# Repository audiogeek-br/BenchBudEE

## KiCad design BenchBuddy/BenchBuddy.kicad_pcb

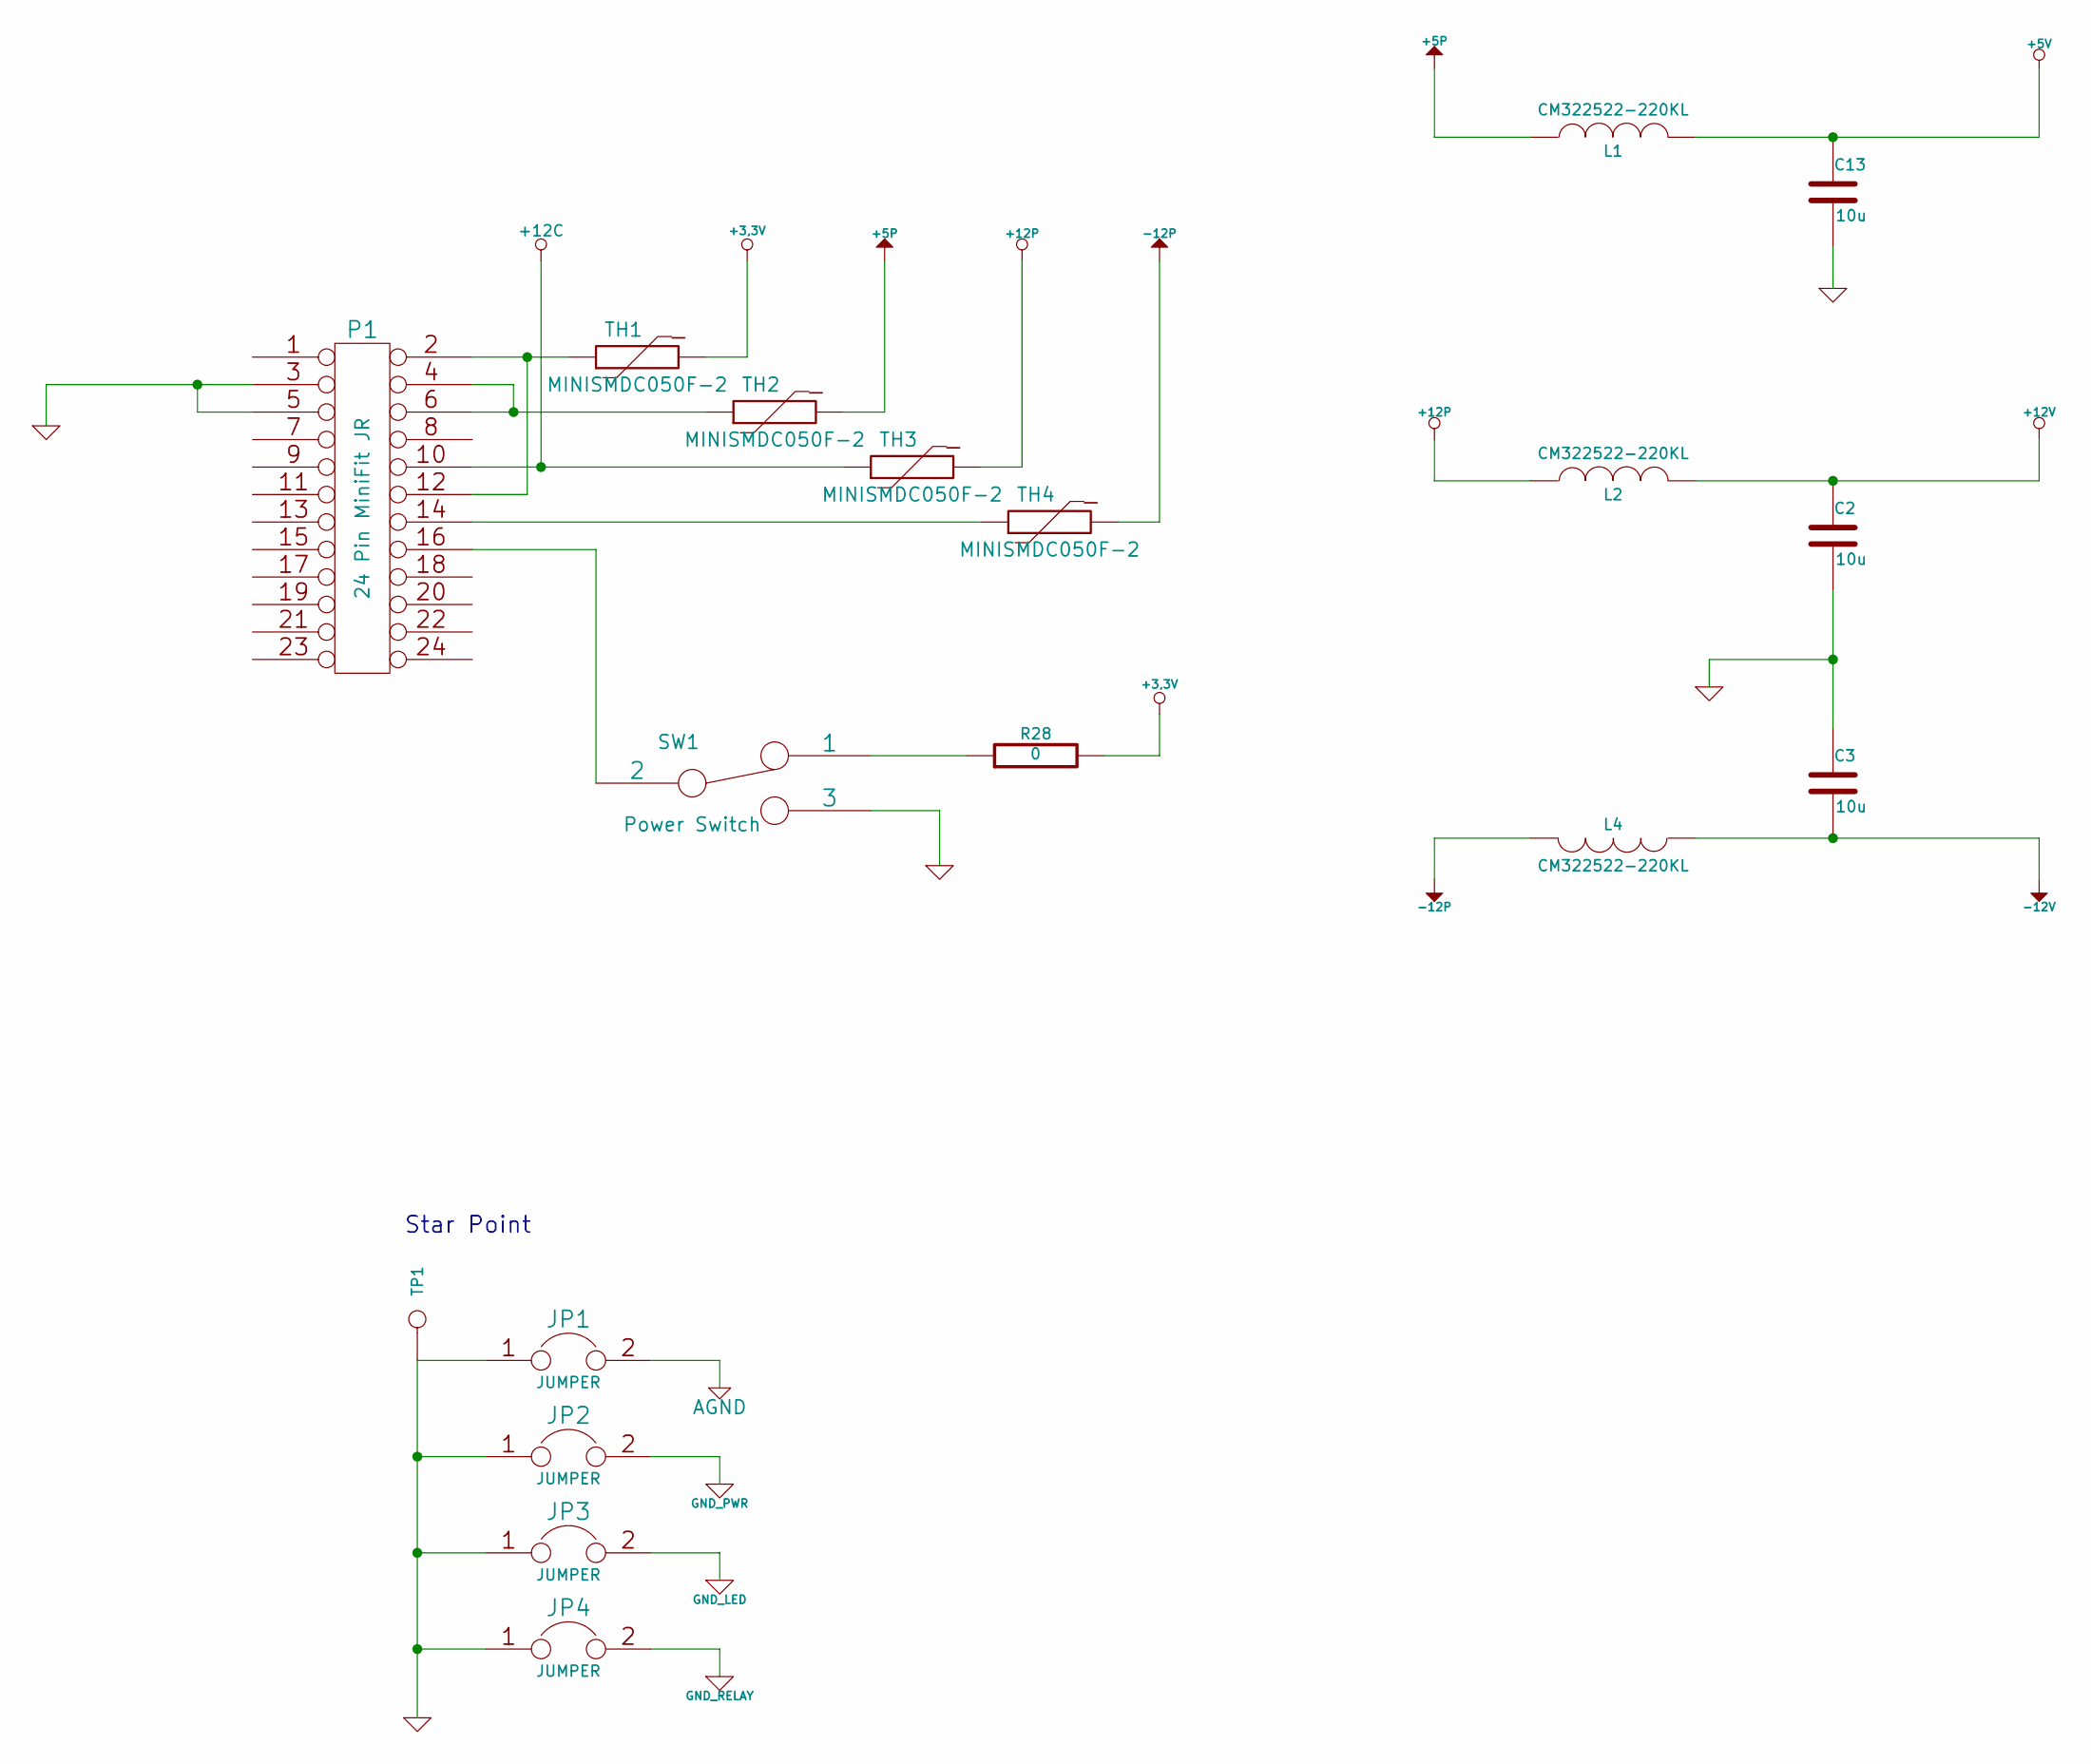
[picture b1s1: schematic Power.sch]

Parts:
C2, C3, C13: 10u
JP1, JP2, JP3, JP4: JUMPER
L1, L2, L4: CM322522-220KL; MFG Part Number CM322522-220KL
P1: 24 Pin MiniFit JR; MFG Part Number 0039301240
R28: 0
SW1: Power Switch; MFG Part Number OS102011MA1QN1
TH1, TH2, TH3, TH4: MINISMDC050F-2; MFG Part Number MINISMDC050F-2
TP1: CONN_1

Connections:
+3.3V: R28.2, TH1.2; also elsewhere on the board
+5P: L1.1, TH2.2; also elsewhere on the board
+5V: C13.1, L1.2; also elsewhere on the board
+12C: P1.10, TH3.1; also elsewhere on the board
+12P: L2.1, TH3.2; also elsewhere on the board
+12V: C2.1, L2.2; also elsewhere on the board
-12P: L4.2, TH4.2
-12V: C3.2, L4.1; also elsewhere on the board
AGND: JP1.2; also elsewhere on the board
GND: C2.2, C3.1, C13.2, JP1.1, JP2.1, JP3.1, JP4.1, P1.3, P1.5, SW1.3, TP1.1; also elsewhere on the board
unnamed: P1.16, SW1.2
unnamed: R28.1, SW1.1
unnamed: P1.14, TH4.1
unnamed: P1.4, P1.6, TH2.1
unnamed: P1.2, P1.12, TH1.1

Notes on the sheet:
Star Point

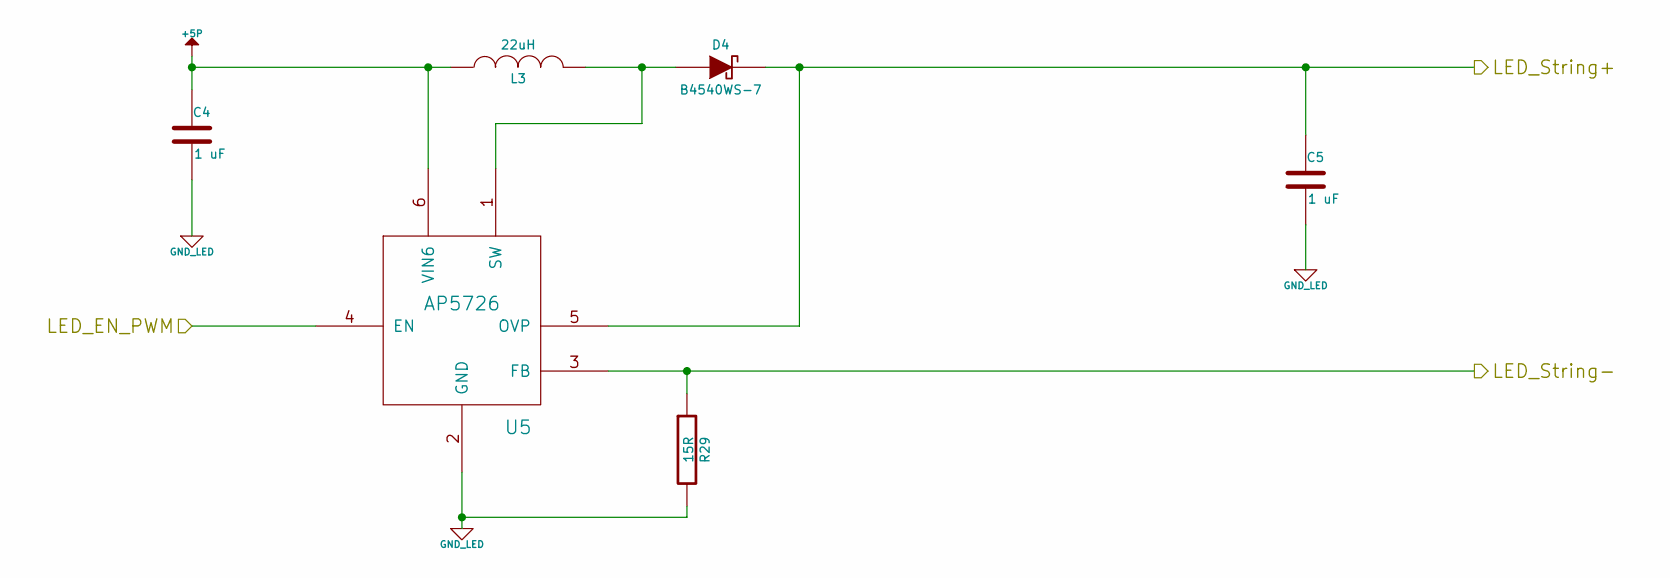
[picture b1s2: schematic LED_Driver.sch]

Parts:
C4, C5: 1 uF
D4: B4540WS-7
L3: 22uH; MFG Part Number NR4012T220M
R29: 15R
U5: AP5726

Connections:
+5P: C4.1, L3.1, U5.6 (VIN6); also elsewhere on the board
/Arduino/LED_EN_PWM: U5.4 (EN); also elsewhere on the board
/Terminal Block/LED_STRING+: C5.1, D4.2 (K), U5.5 (OVP); also elsewhere on the board
/Terminal Block/LED_STRING-: R29.1, U5.3 (FB); also elsewhere on the board
GND_LED: C4.2, C5.2, R29.2, U5.2 (GND)
unnamed: D4.1 (A), L3.2, U5.1 (SW)

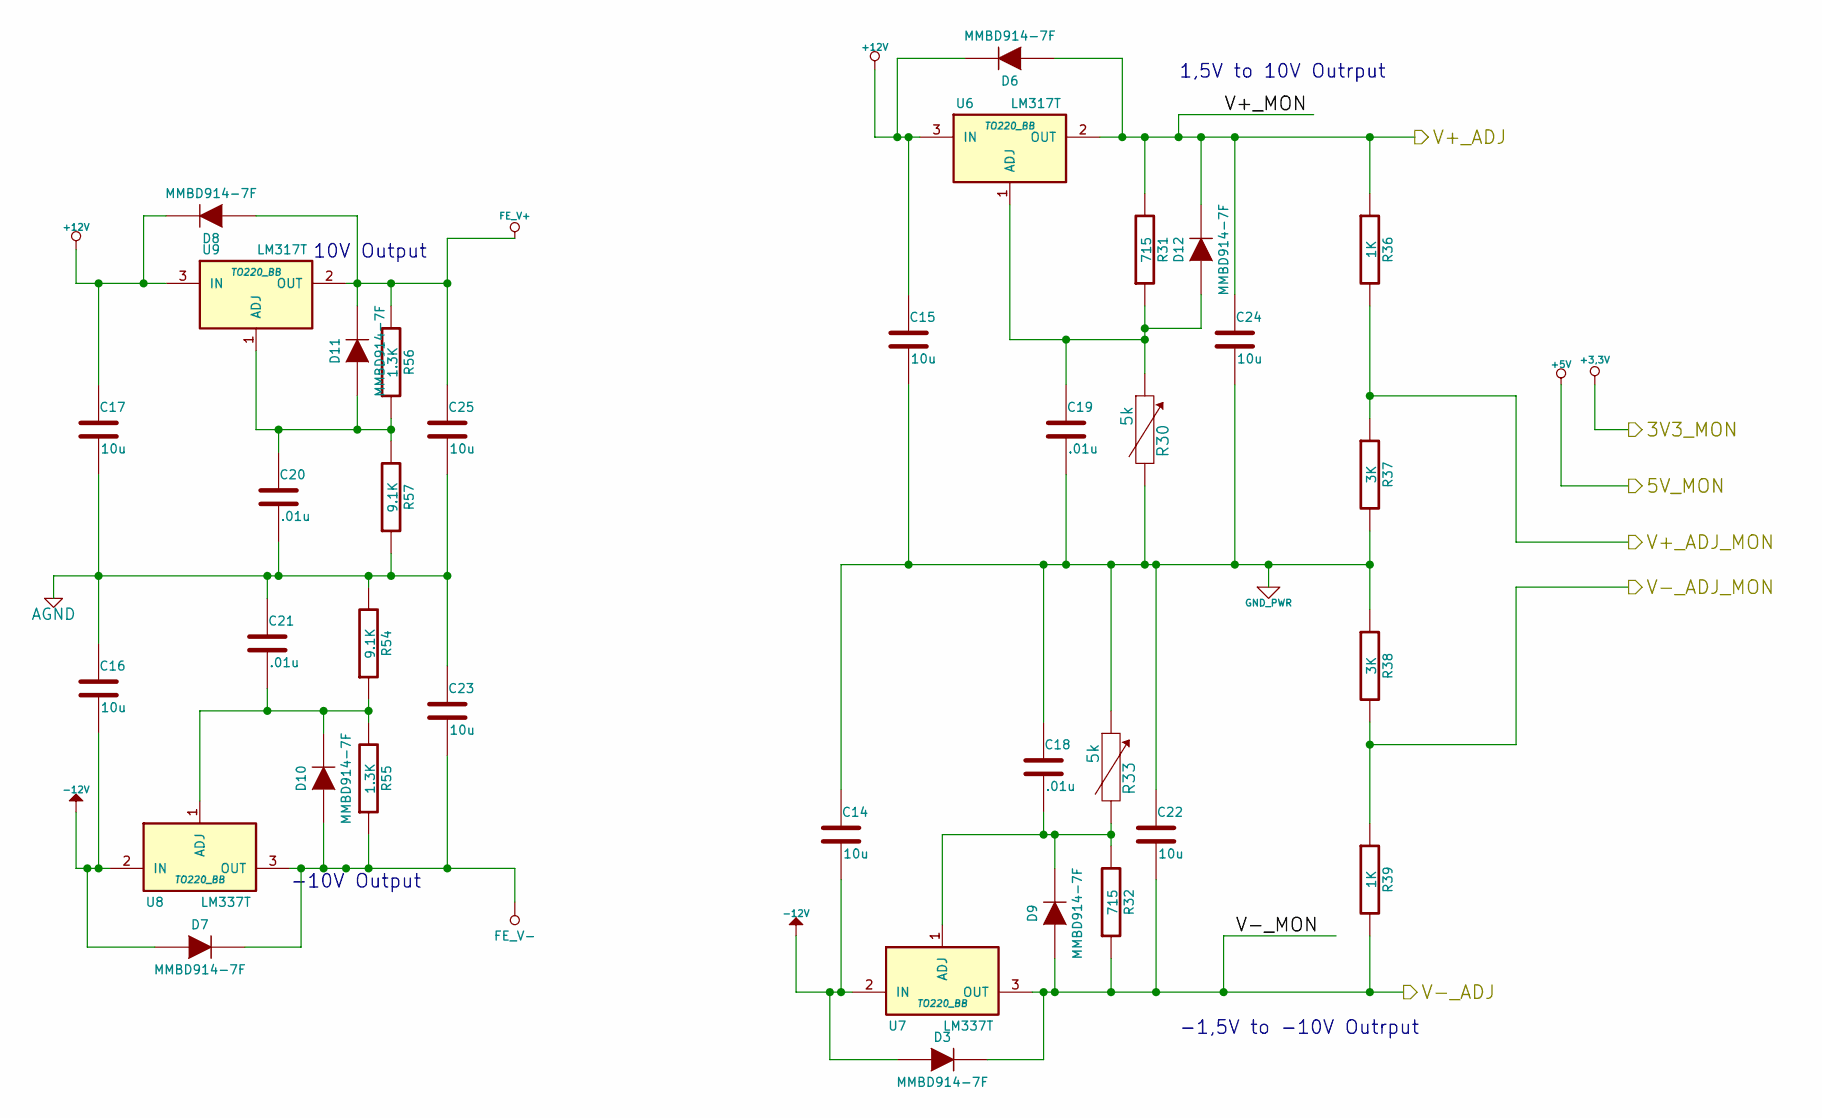
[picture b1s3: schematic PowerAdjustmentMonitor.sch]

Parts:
C14, C15, C16, C17, C22, C23, C24, C25: 10u
C18, C19, C20, C21: .01u
D3, D6, D7, D8, D9, D10, D11, D12: MMBD914-7F
R30, R33: 5k
R31, R32: 715
R36, R39: 1K
R37, R38: 3K
R54, R57: 9.1K
R55, R56: 1.3K
U6, U9: LM317T; TO220_BB
U7, U8: LM337T; TO220_BB

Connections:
+12V: C15.1, C17.1, D6.2 (K), D8.2 (K), U6.3 (IN), U9.3 (IN); also elsewhere on the board
-12V: C14.2, C16.2, D3.1 (A), D7.1 (A), U7.2 (IN), U8.2 (IN); also elsewhere on the board
/Arduino/V+_ADJ_MON: R36.2, R37.1; also elsewhere on the board
/Arduino/V-_ADJ_MON: R38.2, R39.1; also elsewhere on the board
/PowerAdjustmentMonitor/V+_ADJ: C24.1, D6.1 (A), D12.2 (K), R31.2, R36.1, U6.2 (OUT); also elsewhere on the board
/PowerAdjustmentMonitor/V-_ADJ: C22.2, D3.2 (K), D9.1 (A), R32.1, R39.2, U7.3 (OUT); also elsewhere on the board
AGND: C16.1, C17.2, C20.2, C21.1, C23.1, C25.2, R54.2, R57.1; also elsewhere on the board
FE_V+: C25.1, D8.1 (A), D11.2 (K), R56.2, U9.2 (OUT); also elsewhere on the board
FE_V-: C23.2, D7.2 (K), D10.1 (A), R55.1, U8.3 (OUT); also elsewhere on the board
GND_PWR: C14.1, C15.2, C18.1, C19.2, C22.1, C24.2, R30.2, R33.1, R37.2, R38.1; also elsewhere on the board
unnamed: C21.2, D10.2 (K), R54.1, R55.2, U8.1 (ADJ)
unnamed: C20.1, D11.1 (A), R56.1, R57.2, U9.1 (ADJ)
unnamed: C19.1, D12.1 (A), R30.1, R31.1, U6.1 (ADJ)
unnamed: C18.2, D9.2 (K), R32.2, R33.2, U7.1 (ADJ)

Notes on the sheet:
10V Output
1,5V to 10V Outrput
-10V Output
-1,5V to -10V Outrput

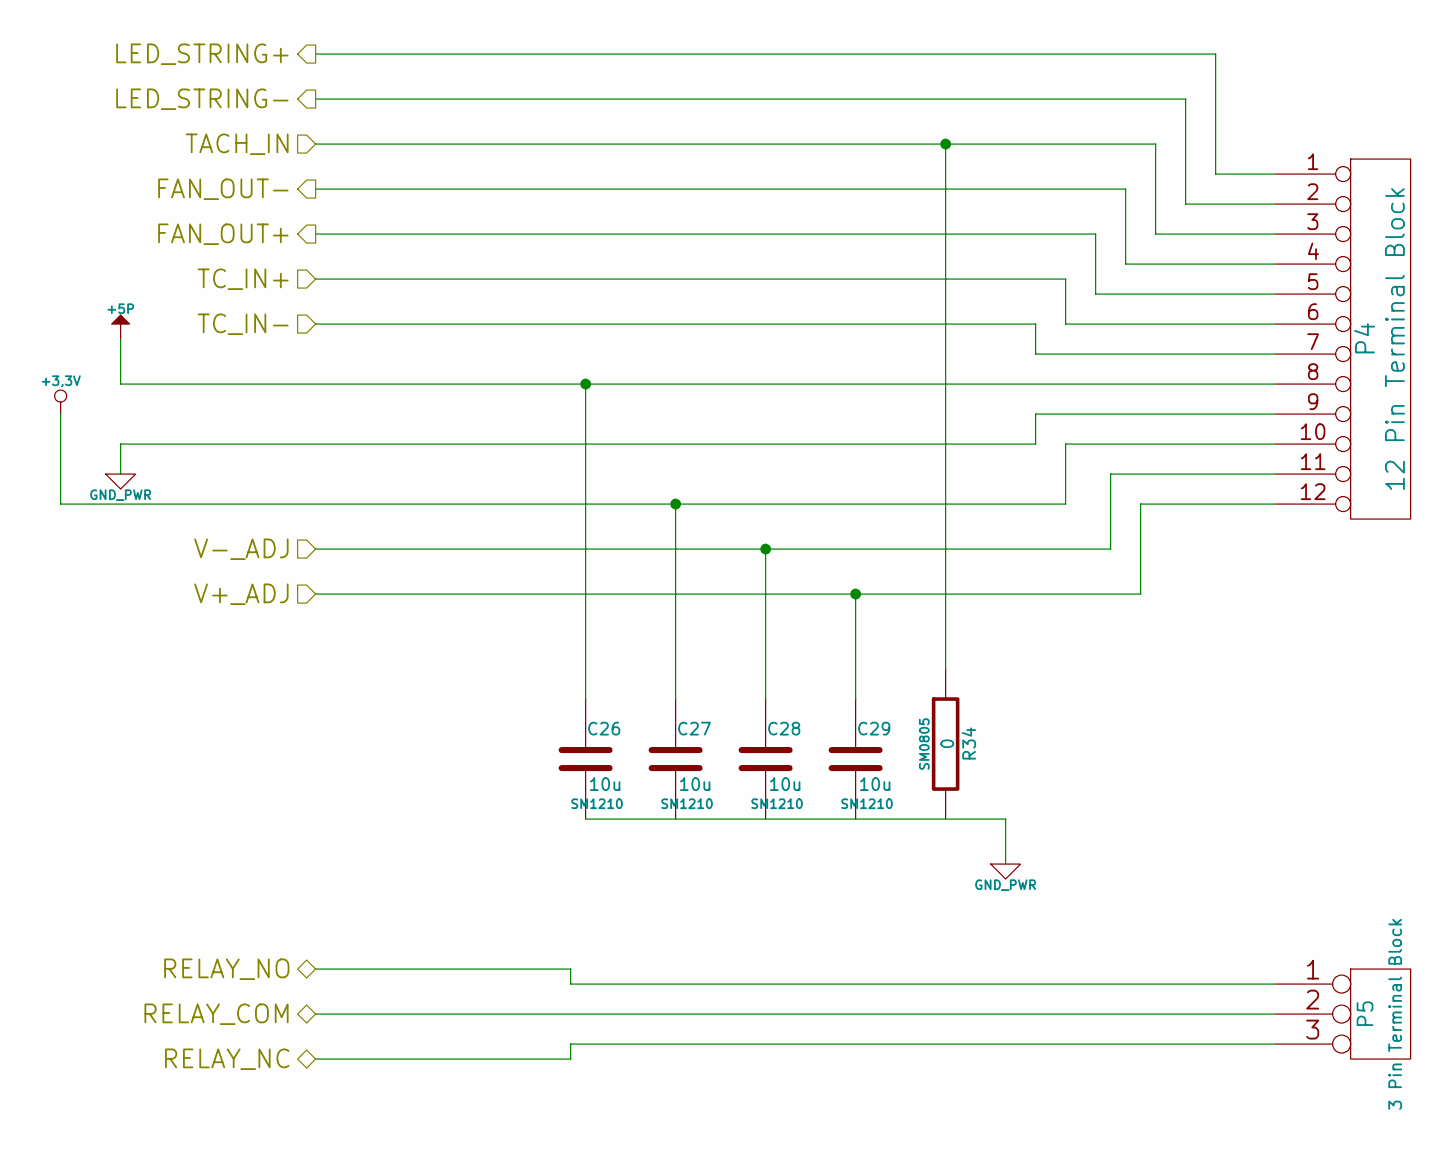
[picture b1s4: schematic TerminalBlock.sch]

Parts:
C26, C27, C28, C29: 10u; SM1210
P4: 12 Pin Terminal Block; MFG Part Number OSTTE120104
P5: 3 Pin Terminal Block; MFG Part Number 1935174
R34: 0; SM0805

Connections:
+3.3V: C27.1, P4.10; also elsewhere on the board
+5P: C26.1, P4.8; also elsewhere on the board
/PowerAdjustmentMonitor/V+_ADJ: C29.1, P4.12; also elsewhere on the board
/PowerAdjustmentMonitor/V-_ADJ: C28.1, P4.11; also elsewhere on the board
/Relay/RELAY_COM: P5.2 (PM); also elsewhere on the board
/Relay/RELAY_NC: P5.3; also elsewhere on the board
/Relay/RELAY_NO: P5.1; also elsewhere on the board
/Terminal Block/FAN_OUT+: P4.5; also elsewhere on the board
/Terminal Block/FAN_OUT-: P4.4; also elsewhere on the board
/Terminal Block/LED_STRING+: P4.1; also elsewhere on the board
/Terminal Block/LED_STRING-: P4.2; also elsewhere on the board
/Terminal Block/TACH_IN: P4.3, R34.1; also elsewhere on the board
/Thermocoulpe/TC IN +: P4.6; also elsewhere on the board
/Thermocoulpe/TC IN -: P4.7; also elsewhere on the board
GND_PWR: C26.2, P4.9; also elsewhere on the board

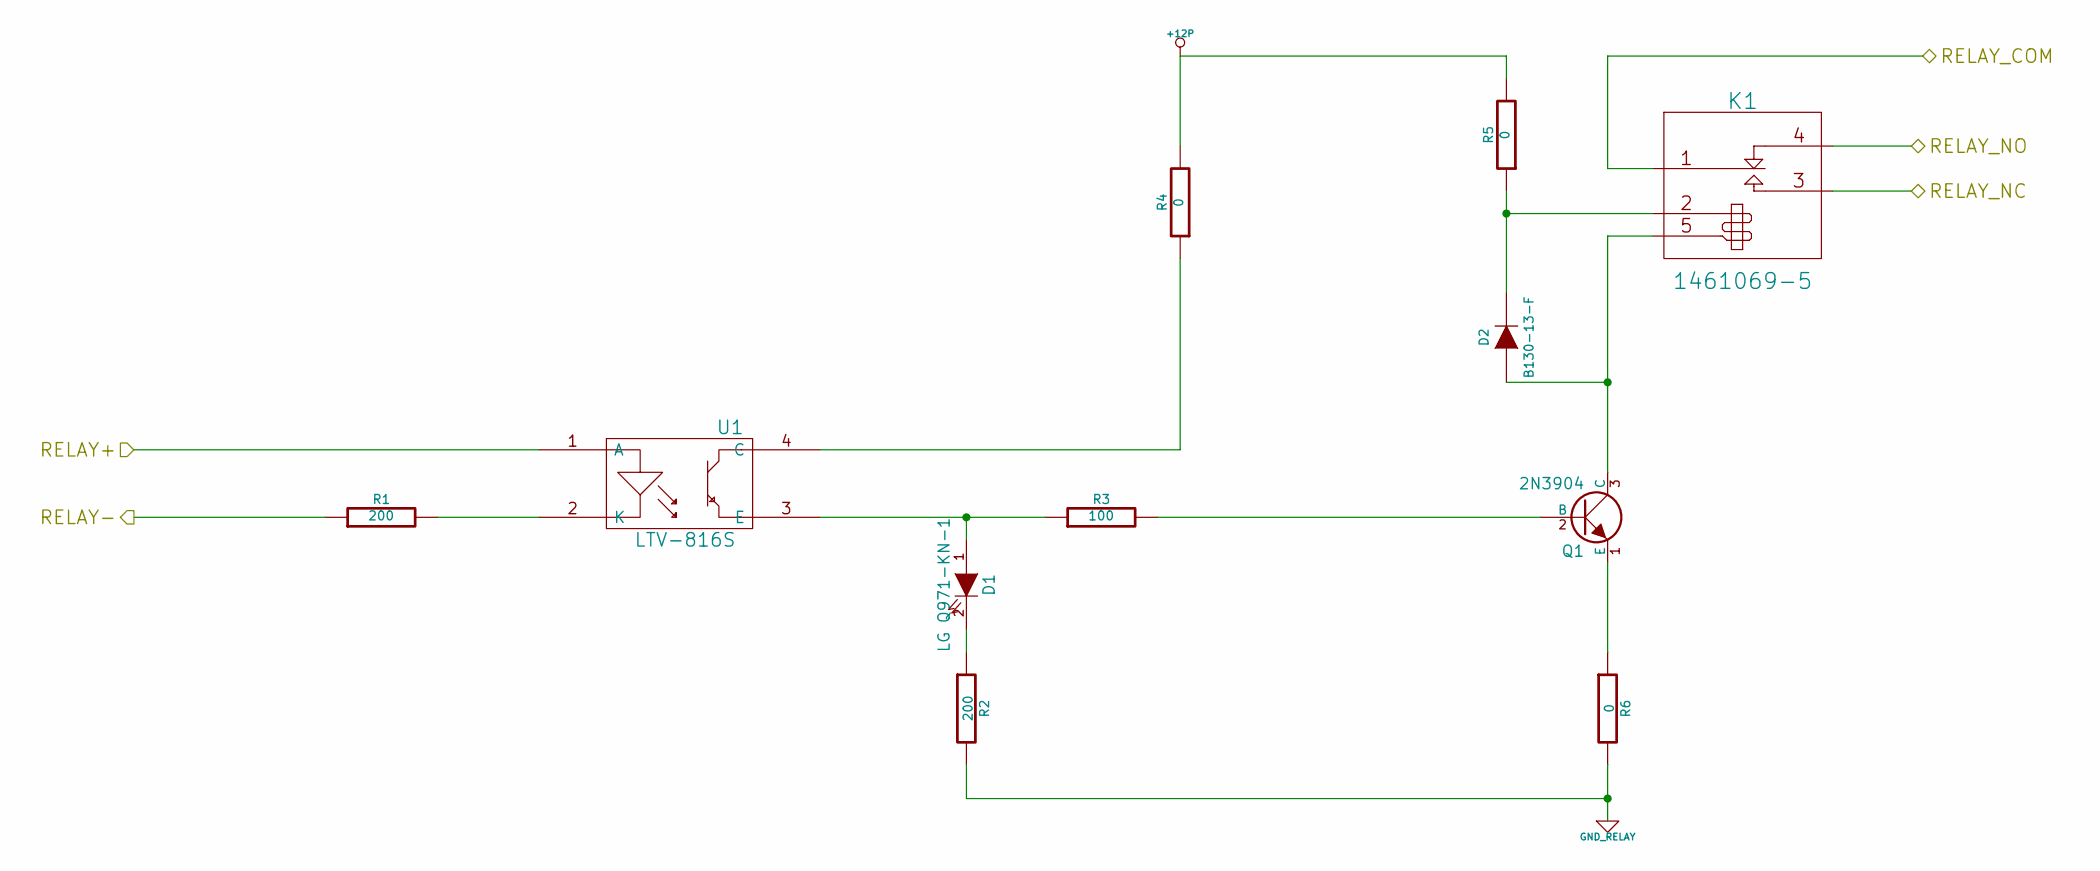
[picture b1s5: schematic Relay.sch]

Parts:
D1: LG Q971-KN-1
D2: B130-13-F
K1: 1461069-5
Q1: 2N3904; MFG Part Number MMBT3904-7-F
R1, R2: 200
R3: 100
R4, R5, R6: 0
U1: LTV-816S; MFG Part Number LTV-816S

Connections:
+12P: R4.2, R5.2; also elsewhere on the board
/Arduino/RELAY+: U1.1 (A); also elsewhere on the board
/Arduino/RELAY-: R1.1; also elsewhere on the board
/Relay/RELAY_COM: K1.1 (COM); also elsewhere on the board
/Relay/RELAY_NC: K1.3 (NO); also elsewhere on the board
/Relay/RELAY_NO: K1.4 (NC); also elsewhere on the board
GND_RELAY: R2.2, R6.2
unnamed: D1.2 (K), R2.1
unnamed: D2.2 (K), K1.2 (COIL_+), R5.1
unnamed: Q1.2 (B), R3.2
unnamed: Q1.1 (E), R6.1
unnamed: D1.1 (A), R3.1, U1.3 (E)
unnamed: R1.2, U1.2 (K)
unnamed: R4.1, U1.4 (C)
unnamed: D2.1 (A), K1.5 (COIL_-), Q1.3 (C)

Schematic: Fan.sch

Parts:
C11, C12, C32: 1u
D5: B130-13-F; MFG Part Number B130-13-F
Q2: DMN65D8L-7; MFG Part Number DMN65D8L-7
Q3, Q4: AOD476; MFG Part Number AOD476
R35, R40, R58, R59: 0
R41: 1
TH5: MINISMDC050F-2; MFG Part Number MINISMDC050F-2
U4: OPA4170
U11: MCP4801

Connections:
+5V: C11.1, U11.1 (Vdd); also elsewhere on the board
+12C: C12.1, TH5.1; also elsewhere on the board
/Arduino/CURR_MEAS: Q3.2, Q4.3, R41.1, R59.2; also elsewhere on the board
/Arduino/FAN_MODE: Q3.1; also elsewhere on the board
/Arduino/FAN_PWM: Q2.G; also elsewhere on the board
/Arduino/MOSI: U11.4 (SDI); also elsewhere on the board
/Arduino/SCLK: U11.3 (SCK); also elsewhere on the board
/Arduino/~LADC: U11.5 (~LDAC); also elsewhere on the board
/Arduino/~SHDN: U11.6 (~SHDN); also elsewhere on the board
/Fan/CS_N: U11.2 (~CS); also elsewhere on the board
/Terminal Block/FAN_OUT+: D5.2 (K), TH5.2; also elsewhere on the board
/Terminal Block/FAN_OUT-: D5.1 (A), Q4.2; also elsewhere on the board
AGND: C12.2, Q3.3, R35.2, R41.2, U11.7 (Vss); also elsewhere on the board
FE_V+: U4.4 (V+); also elsewhere on the board
FE_V-: U4.11 (V-); also elsewhere on the board
unnamed: Q2.S, R35.1
unnamed: C32.1, R58.1, U4.7
unnamed: C32.2, R59.1, U4.6 (-)
unnamed: R40.1, U11.8 (Vout)
unnamed: Q2.D, R40.2, U4.5 (+)

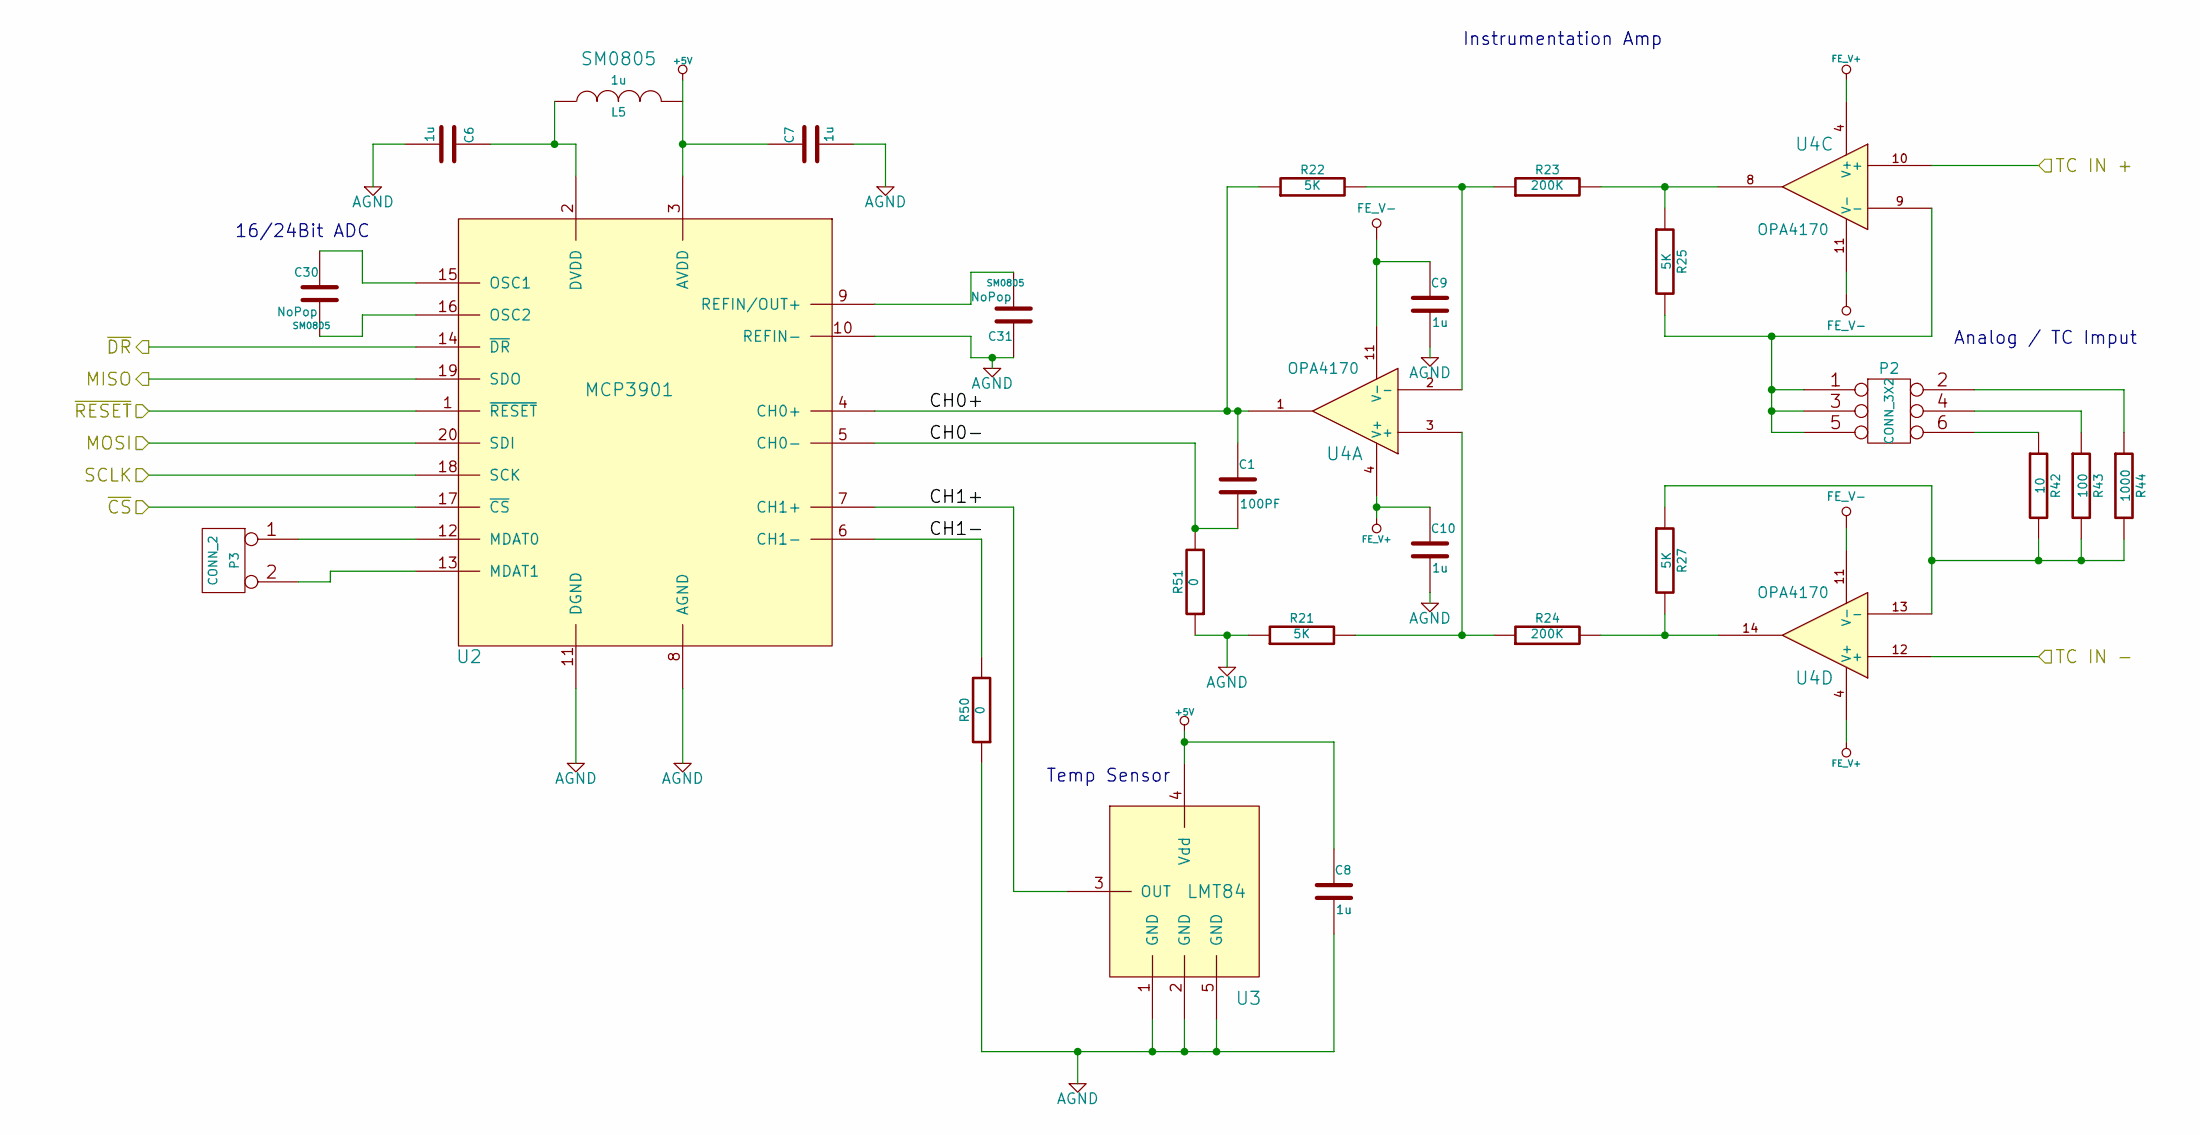
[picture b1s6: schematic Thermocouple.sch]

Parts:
C1: 100PF
C6, C7, C8, C9, C10: 1u
C30, C31: NoPop; SM0805
L5: 1u; SM0805
P2: CONN_3X2
P3: CONN_2
R21, R22, R25, R27: 5K
R23, R24: 200K
R42: 10
R43: 100
R44: 1000
R50, R51: 0
U2: MCP3901
U3: LMT84
U4: OPA4170

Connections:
+5V: C7.1, C8.1, U2.3 (AVDD), U3.4 (Vdd); also elsewhere on the board
/Arduino/MISO: U2.19 (SDO); also elsewhere on the board
/Arduino/MOSI: U2.20 (SDI); also elsewhere on the board
/Arduino/SCLK: U2.18 (SCK); also elsewhere on the board
/Arduino/~ADC_CS: U2.17 (~CS); also elsewhere on the board
/Arduino/~DR: U2.14 (~DR); also elsewhere on the board
/Arduino/~RESET: U2.1 (~RESET); also elsewhere on the board
/Thermocoulpe/CH0+: C1.1, R22.1, U2.4 (CH0+), U4.1
/Thermocoulpe/CH0-: C1.2, R51.2, U2.5 (CH0-)
/Thermocoulpe/CH1+: U2.7 (CH1+), U3.3 (OUT)
/Thermocoulpe/CH1-: R50.2, U2.6 (CH1-)
/Thermocoulpe/TC IN +: U4.10 (+); also elsewhere on the board
/Thermocoulpe/TC IN -: U4.12 (+); also elsewhere on the board
AGND: C6.2, C7.2, C8.2, C9.2, C10.2, C31.1, R21.1, R50.1, R51.1, U2.8 (AGND), U2.10 (REFIN-), U2.11 (DGND), U3.1 (GND), U3.2 (GND), U3.5 (GND); also elsewhere on the board
FE_V+: C10.1, U4.4 (V+); also elsewhere on the board
FE_V-: C9.1, U4.11 (V-); also elsewhere on the board
unnamed: P3.1, U2.12 (MDAT0)
unnamed: P3.2 (PM), U2.13 (MDAT1)
unnamed: C31.2, U2.9 (REFIN/OUT+)
unnamed: C6.1, L5.1, U2.2 (DVDD)
unnamed: C30.1, U2.15 (OSC1)
unnamed: C30.2, U2.16 (OSC2)
unnamed: P2.4, R43.1
unnamed: P2.6, R42.1
unnamed: R27.1, R42.2, R43.2, R44.2, U4.13 (-)
unnamed: P2.2, R44.1
unnamed: P2.1, P2.3, P2.5, R25.2, U4.9 (-)
unnamed: R24.2, R27.2, U4.14
unnamed: R23.2, R25.1, U4.8
unnamed: R22.2, R23.1, U4.2 (-)
unnamed: R21.2, R24.1, U4.3 (+)

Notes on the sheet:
Analog / TC Imput
Instrumentation Amp
16/24Bit ADC
Temp Sensor

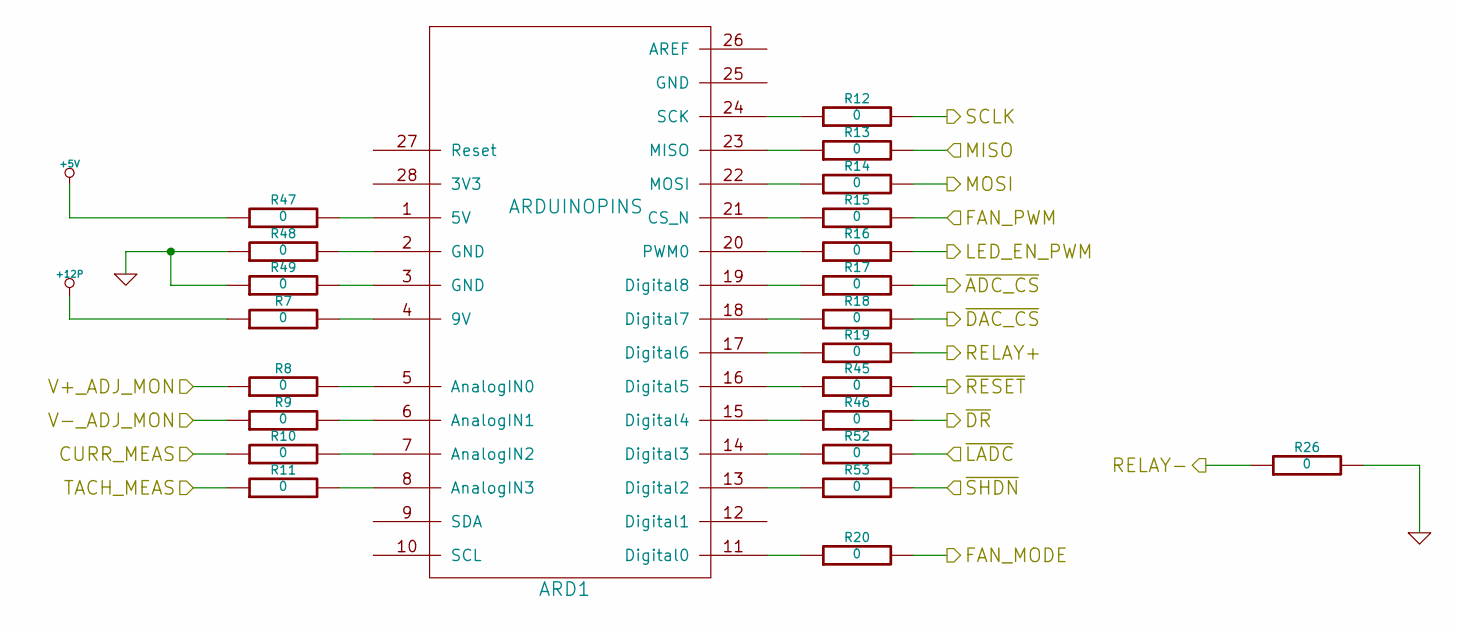
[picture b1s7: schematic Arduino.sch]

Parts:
ARD1: ARDUINOPINS
R7, R8, R9, R10, R11, R12, R13, R14, R15, R16, R17, R18, R19, R20, R26, R45, R46, R47, R48, R49, R52, R53: 0

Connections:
+5V: R47.1; also elsewhere on the board
+12P: R7.1; also elsewhere on the board
/Arduino/CURR_MEAS: R10.1; also elsewhere on the board
/Arduino/FAN_MODE: R20.2; also elsewhere on the board
/Arduino/FAN_PWM: R15.2; also elsewhere on the board
/Arduino/LED_EN_PWM: R16.2; also elsewhere on the board
/Arduino/MISO: R13.2; also elsewhere on the board
/Arduino/MOSI: R14.2; also elsewhere on the board
/Arduino/RELAY+: R19.2; also elsewhere on the board
/Arduino/RELAY-: R26.1; also elsewhere on the board
/Arduino/SCLK: R12.2; also elsewhere on the board
/Arduino/V+_ADJ_MON: R8.1; also elsewhere on the board
/Arduino/V-_ADJ_MON: R9.1; also elsewhere on the board
/Arduino/~ADC_CS: R17.2; also elsewhere on the board
/Arduino/~DR: R46.2; also elsewhere on the board
/Arduino/~LADC: R52.2; also elsewhere on the board
/Arduino/~RESET: R45.2; also elsewhere on the board
/Arduino/~SHDN: R53.2; also elsewhere on the board
/Fan/CS_N: R18.2; also elsewhere on the board
/Terminal Block/TACH_IN: R11.1; also elsewhere on the board
GND: R26.2, R48.1, R49.1; also elsewhere on the board
unnamed: ARD1.7 (AnalogIN2), R10.2
unnamed: ARD1.8 (AnalogIN3), R11.2
unnamed: ARD1.21 (CS_N), R15.1
unnamed: ARD1.17 (Digital6), R19.1
unnamed: ARD1.6 (AnalogIN1), R9.2
unnamed: ARD1.5 (AnalogIN0), R8.2
unnamed: ARD1.4 (9V), R7.2
unnamed: ARD1.20 (PWM0), R16.1
unnamed: ARD1.15 (Digital4), R46.1
unnamed: ARD1.19 (Digital8), R17.1
unnamed: ARD1.18 (Digital7), R18.1
unnamed: ARD1.16 (Digital5), R45.1
unnamed: ARD1.24 (SCK), R12.1
unnamed: ARD1.23 (MISO), R13.1
unnamed: ARD1.13 (Digital2), R53.1
unnamed: ARD1.22 (MOSI), R14.1
unnamed: ARD1.11 (Digital0), R20.1
unnamed: ARD1.1 (5V), R47.2
unnamed: ARD1.2 (GND), R48.2
unnamed: ARD1.3 (GND), R49.2
unnamed: ARD1.14 (Digital3), R52.1

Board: 4 copper layers, 137 parts (53 on the bottom side), 104 nets, no tracks yet.

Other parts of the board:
3 mm, 3 mm#2, 3 mm#3, 3 mm#4: VAL**; 3mm_NPTH

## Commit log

2014-02-01 Creation of Initial Blank Files
2014-02-04 Schematic Skeleton
2014-03-05 Week3 part 1
2014-03-07 Week3 Part 2
2014-03-10 Colocação dos Componentes Relé
2014-03-30 Pre layout
2014-04-23 Pre layout 2
